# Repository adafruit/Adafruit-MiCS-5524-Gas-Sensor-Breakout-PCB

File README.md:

## Adafruit MiCS 5524 Gas Sensor Breakout PCB
<a href="http://www.adafruit.com/products/3199"><br/>
Click here to purchase one from the Adafruit shop</a>

Give your next sensor project a nose for gasses with the Adafruit MiCS-5524 Gas Sensor Breakout. This breakout makes it easy to use this nice sensor from SGX Sensortech. The MiCS-5524 is a robust MEMS sensor for indoor carbon monoxide and natural gas leakage detection, it's suitable also for indoor air quality monitoring; breath checker and early fire detection.

Please note: This sensor is sensitive to CO ( ~ 1 to 1000 ppm), Ammonia (~ 1 to 500 ppm), Ethanol (~ 10 to 500 ppm), H2 (~ 1 - 1000 ppm), and Methane / Propane / Iso-Butane (~ 1,000++ ppm). However, it can't tell you which gas it has detected. 

PCB files for the Adafruit MiCS-5524 Gas Sensor Breakout. The format is EagleCAD schematic and board layout
- https://www.adafruit.com/product/3199

### License

Adafruit invests time and resources providing this open source design, please support Adafruit and open-source hardware by purchasing products from [Adafruit](https://www.adafruit.com)!

All text above must be included in any redistribution

Designed by Limor Fried/Ladyada for Adafruit Industries.
Creative Commons Attribution/Share-Alike, all text above must be included in any redistribution. 
See license.txt for additional information.

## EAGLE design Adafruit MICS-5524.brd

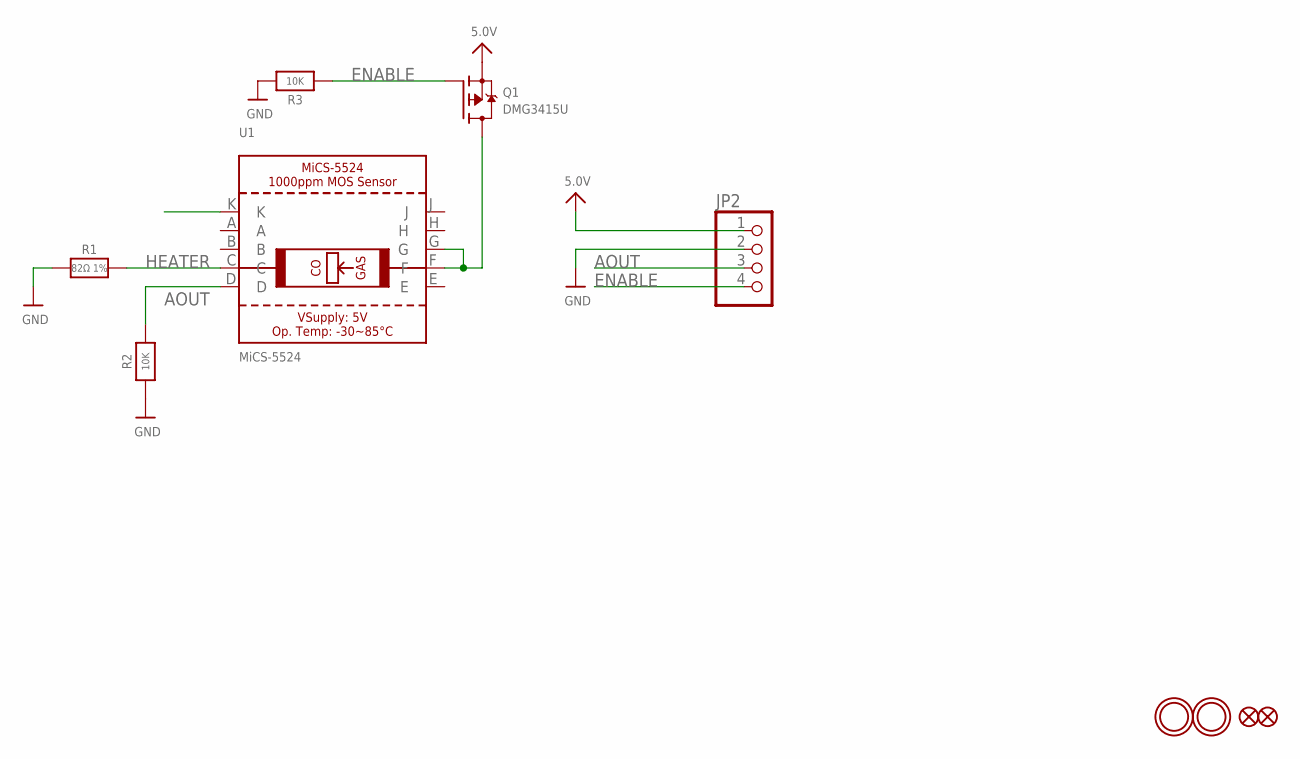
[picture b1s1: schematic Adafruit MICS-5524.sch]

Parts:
FID1, FID2: FIDUCIAL""; FIDUCIAL_1MM
JP2: HEADER-1X476MIL; 1X04_ROUND_76
Q1: DMG3415U; SOT23-WIDE
R1: 82Ω 1%; 0805-NO
R2, R3: 10K; 0805-NO
U1: MiCS-5524; MICS-5524
U$3, U$4: MOUNTINGHOLE2.5; MOUNTINGHOLE_2.5_PLATED

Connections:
5.0V: JP2.1, Q1.2 (S)
AOUT: JP2.3, R2.2, U1.D
ENABLE: JP2.4, Q1.1 (G), R3.1
GND: JP2.2, R1.1, R2.1, R3.2
HEATER: R1.2, U1.C
unnamed: Q1.3 (D), U1.F, U1.G

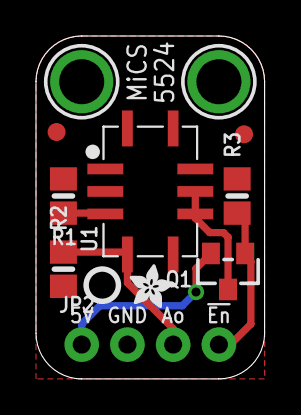
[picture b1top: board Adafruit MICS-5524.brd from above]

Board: 2 copper layers, 12.7 x 19.1 mm, 12 parts (0 on the bottom side), 6 nets.

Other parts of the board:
U$7: ADAFRUIT_2.5MM
U$10: PCBFEAT-REV-040

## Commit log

2016-07-13 gasinit

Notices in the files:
parts and their libraries:
microbuilder: This work is placed in the public domain, and may be freely used for commercial and non-commercial work with the following conditions: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
